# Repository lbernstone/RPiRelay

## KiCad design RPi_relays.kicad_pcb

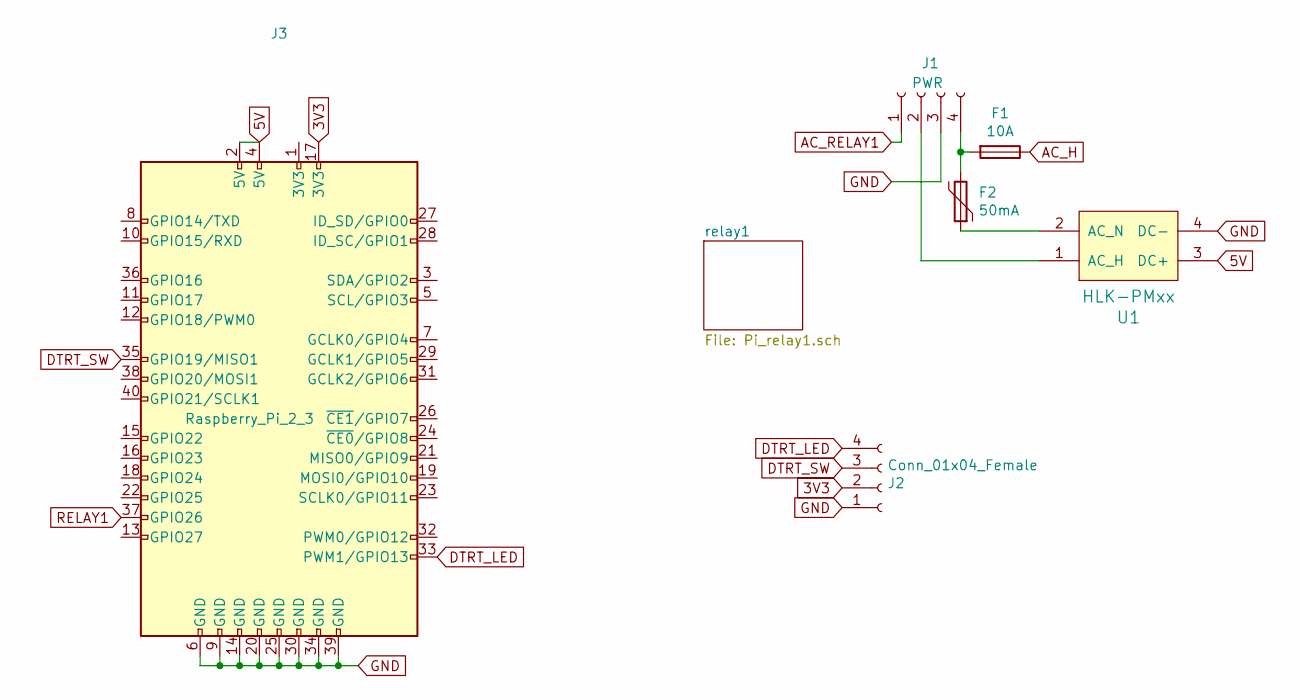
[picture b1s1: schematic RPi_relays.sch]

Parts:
F1: 10A; Fuse_2512_6332Metric
F2: 50mA; Littelfuse_LVR008NS
J1: PWR; TerminalBlock_MetzConnect_Type094_RT03504HBLU_1x04_P5.00mm_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
J2: Conn_01x04_Female; Molex_Micro-Fit_3.0_43045-0412_2x02_P3.00mm_Vertical
J3: Raspberry_Pi_2_3; PinSocket_2x20_P2.54mm_Vertical
U1: HLK-PMxx; HLK-PM01

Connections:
3V3: J2.2, J3.17 (3V3)
5V: J3.2 (5V), J3.4 (5V), U1.3 (DC+); also elsewhere on the board
AC_H: F1.1; also elsewhere on the board
AC_RELAY1: J1.1; also elsewhere on the board
DTRT_LED: J2.4, J3.33 (PWM1/GPIO13)
DTRT_SW: J2.3, J3.35 (GPIO19/MISO1)
GND: J1.3, J2.1, J3.6 (GND), J3.9 (GND), J3.14 (GND), J3.20 (GND), J3.25 (GND), J3.30 (GND), J3.34 (GND), J3.39 (GND), U1.4 (DC-); also elsewhere on the board
unnamed: F1.2, F2.2, J1.4
unnamed: F2.1, U1.2 (AC_N)
unnamed: J1.2, U1.1 (AC_H)
RELAY1: J3.37 (GPIO26); also elsewhere on the board

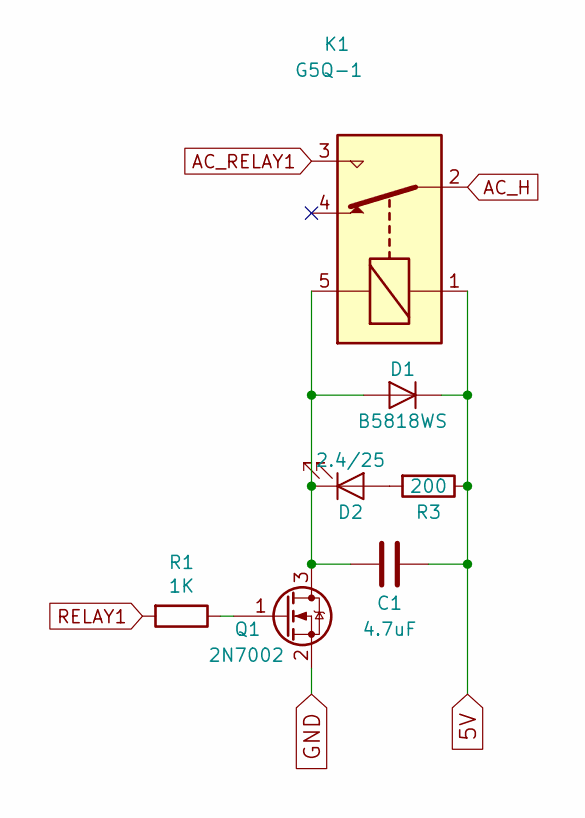
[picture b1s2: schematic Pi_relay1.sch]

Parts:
C1: 4.7uF; C_0805_2012Metric
D1: B5818WS; D_SOD-323
D2: 2.4/25; LED_1206_3216Metric
K1: G5Q-1; SRD-05VDC-SL-C
Q1: 2N7002; TSOT-23
R1: 1K; R_0805_2012Metric
R3: 200; R_0805_2012Metric

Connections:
5V: C1.1, D1.1 (K), K1.1, R3.1; also elsewhere on the board
AC_H: K1.2; also elsewhere on the board
AC_RELAY1: K1.3; also elsewhere on the board
GND: Q1.2 (S); also elsewhere on the board
unnamed: C1.2, D1.2 (A), D2.1 (K), K1.5, Q1.3 (D)
unnamed: D2.2 (A), R3.2
unnamed: Q1.1 (G), R1.1
RELAY1: R1.2; also elsewhere on the board

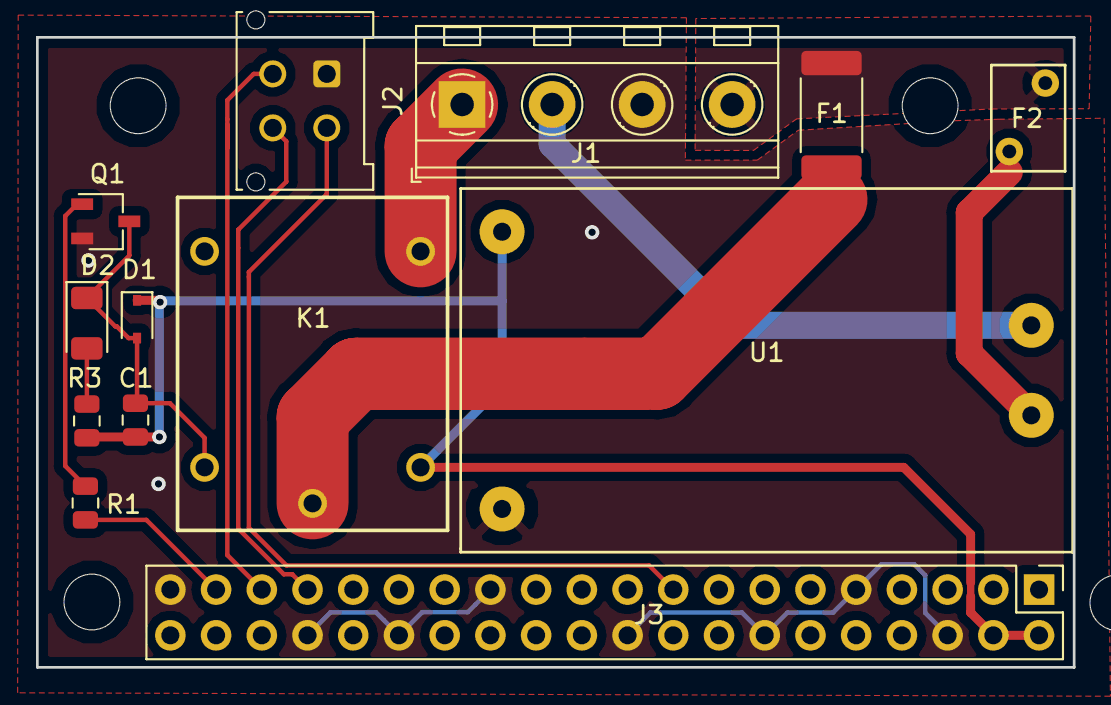
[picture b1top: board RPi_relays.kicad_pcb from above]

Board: 2 copper layers, 57.6 x 35.0 mm, 13 parts (0 on the bottom side), 14 nets.

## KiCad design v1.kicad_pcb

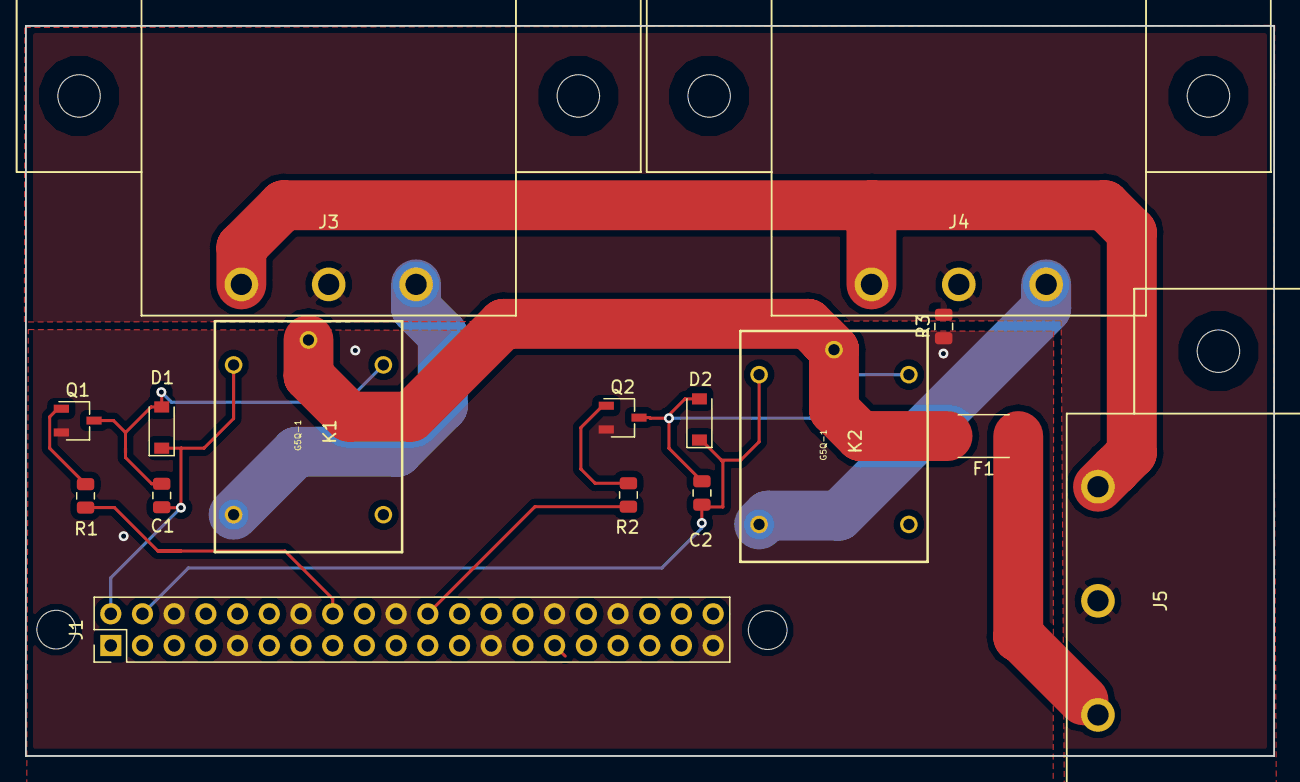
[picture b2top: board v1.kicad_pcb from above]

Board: 2 copper layers, 100.0 x 58.5 mm, 16 parts (0 on the bottom side), 15 nets.

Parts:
C1, C2: 4.7uF; C_0805_2012Metric
D1, D2: B5818WS; D_SOD-123
F1: 10A; Fuse_2512_6332Metric
J1: Raspberry_Pi_2_3; Raspberry_PI_header
J3, J4: Conn_01x03_Female; PX0675_PC
J5: Conn_01x03_Female; PX0580_PC
K1, K2: G5Q-1; SRD-05VDC-SL-C
Q1, Q2: 2N7002; TSOT-23
R1, R2: 2K; R_0805_2012Metric
R3: 10K; R_0805_2012Metric

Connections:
3V3: J1.1, J1.17
5V: C1.1, C2.1, D1.1, D2.1, J1.2, J1.4, K1.1, K2.1
AC_H: F1.2, K1.2, K2.2
AC_RELAY1: J3.1, K1.3
AC_RELAY2: J4.1, K2.3
GND: J1.6, J1.9, J1.14, J1.20, J1.25, J1.30, J1.34, J1.39, Q1.2, Q2.2, R3.1
unnamed: C1.2, D1.2, K1.5, Q1.3
unnamed: C2.2, D2.2, K2.5, Q2.3
unnamed: F1.1, J5.1
unnamed: J3.2, J4.2, J5.2, R3.2
unnamed: J3.3, J4.3, J5.3
unnamed: Q1.1, R1.1
unnamed: Q2.1, R2.1
RELAY1: J1.16, R1.2
RELAY2: J1.22, R2.2

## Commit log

2019-08-12 Button added
